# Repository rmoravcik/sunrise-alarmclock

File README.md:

Sunrise Alarm Clock

A [Philips Wake-Up Light](http://www.usa.philips.com/c-p/HF3505_60/wake-up-light) inspired alarm clock based on:

* Atmel ATmega328p
* RTC DS1307
* Bluetooth module HC-05 for remote configuration (Android application)
* WTV020 MP3 module for audio output

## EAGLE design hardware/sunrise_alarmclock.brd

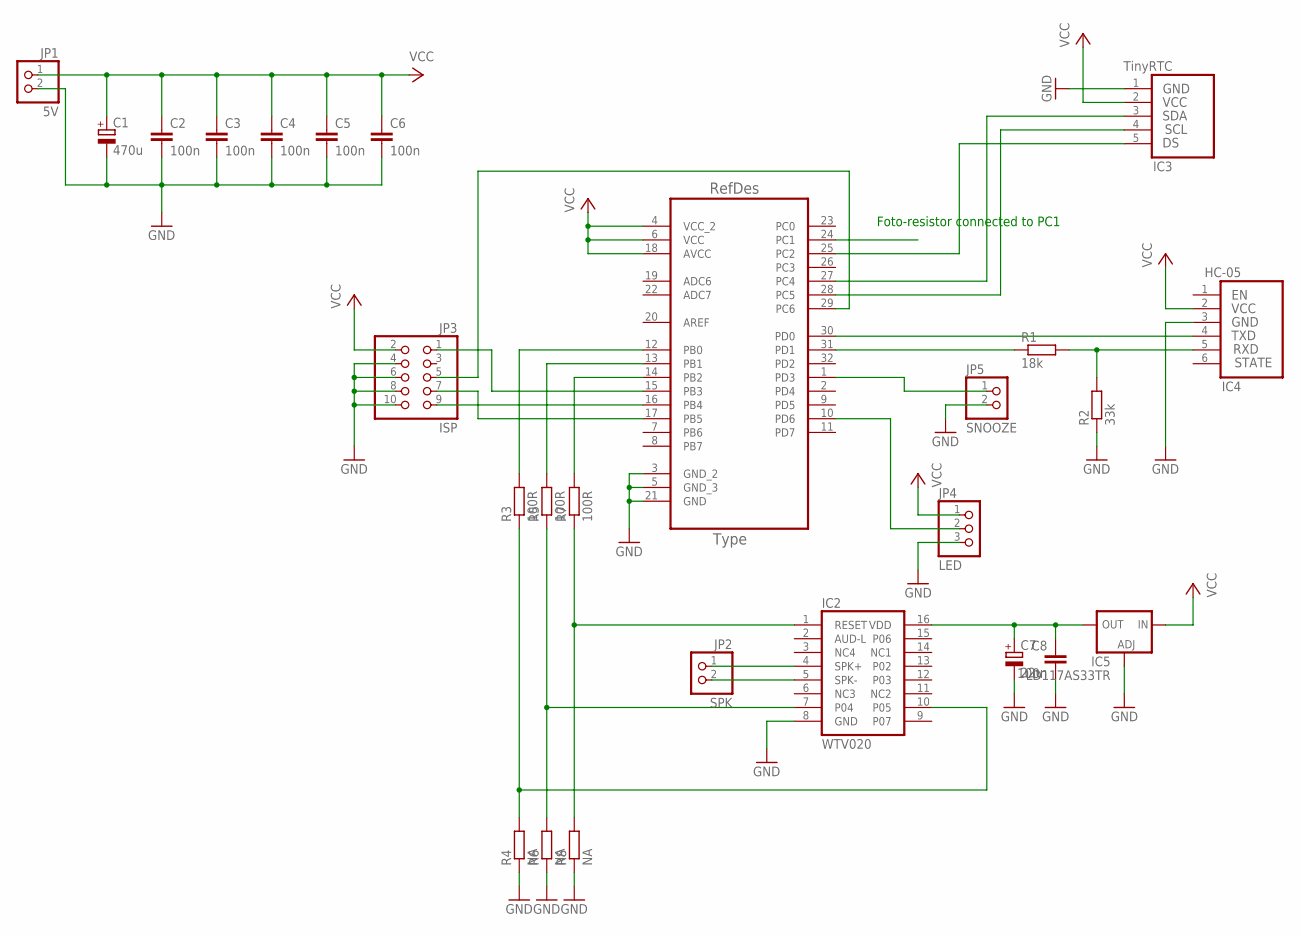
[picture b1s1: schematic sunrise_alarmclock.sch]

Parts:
C1: 470u; D/7343-31W
C2, C3, C4, C5, C6, C8: 100n; C1206K
C7: 22u; C/6032-28R
IC1: ATMEGA328P; QFP80P900X900X120-32N
IC2: WTV020; DIL16-6
IC3: TinyRTC; HC-05
IC4: HC-05
IC5: LD117AS33TR; SOT223
JP1: 5V; 1X02
JP2: SPK; 1X02
JP3: ISP; 2X05
JP4: LED; 1X03
JP5: SNOOZE; 1X02
R1: 18k; M1206
R2: 33k; M1206
R3, R5, R7: 100R; M1206
R4, R6, R8: NA; M1206

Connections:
GND: C1.-, C2.2, C3.2, C4.2, C5.2, C6.2, C7.-, C8.2, IC1.3 (GND_2), IC1.5 (GND_3), IC1.21 (GND), IC2.8 (GND), IC3.1 (GND), IC4.3 (GND), IC5.1 (ADJ), JP1.2, JP3.4, JP3.6, JP3.8, JP3.10, JP4.3, JP5.2, R2.1, R4.1, R6.1, R8.1
unnamed: IC1.15 (PB3), JP3.1
unnamed: IC1.29 (PC6), JP3.5
unnamed: IC1.17 (PB5), JP3.7
unnamed: IC1.16 (PB4), JP3.9
unnamed: IC1.31 (PD1), R1.1
unnamed: IC4.5 (RXD), R1.2, R2.2
unnamed: IC2.4 (SPK+), JP2.1
unnamed: IC1.28 (PC5), IC3.4 (SCL)
unnamed: IC1.27 (PC4), IC3.3 (SDA)
unnamed: IC2.5 (SPK-), JP2.2
unnamed: IC2.1 (RESET), R7.1, R8.2
unnamed: IC1.30 (PD0), IC4.4 (TXD)
unnamed: IC2.7 (P04), R5.1, R6.2
unnamed: IC2.10 (P05), R3.1, R4.2
unnamed: IC1.12 (PB0), R3.2
unnamed: IC1.25 (PC2), IC3.5 (DS)
unnamed: C7.+, C8.1, IC2.16 (VDD), IC5.4 (OUT)
unnamed: IC1.13 (PB1), R5.2
unnamed: IC1.14 (PB2), R7.2
unnamed: IC1.10 (PD6), JP4.2
unnamed: IC1.1 (PD3), JP5.1
VCC: C1.+, C2.1, C3.1, C4.1, C5.1, C6.1, IC1.4 (VCC_2), IC1.6 (VCC), IC1.18 (AVCC), IC3.2 (VCC), IC4.2 (VCC), IC5.3 (IN), JP1.1, JP3.2, JP4.1

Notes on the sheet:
Foto-resistor connected to PC1

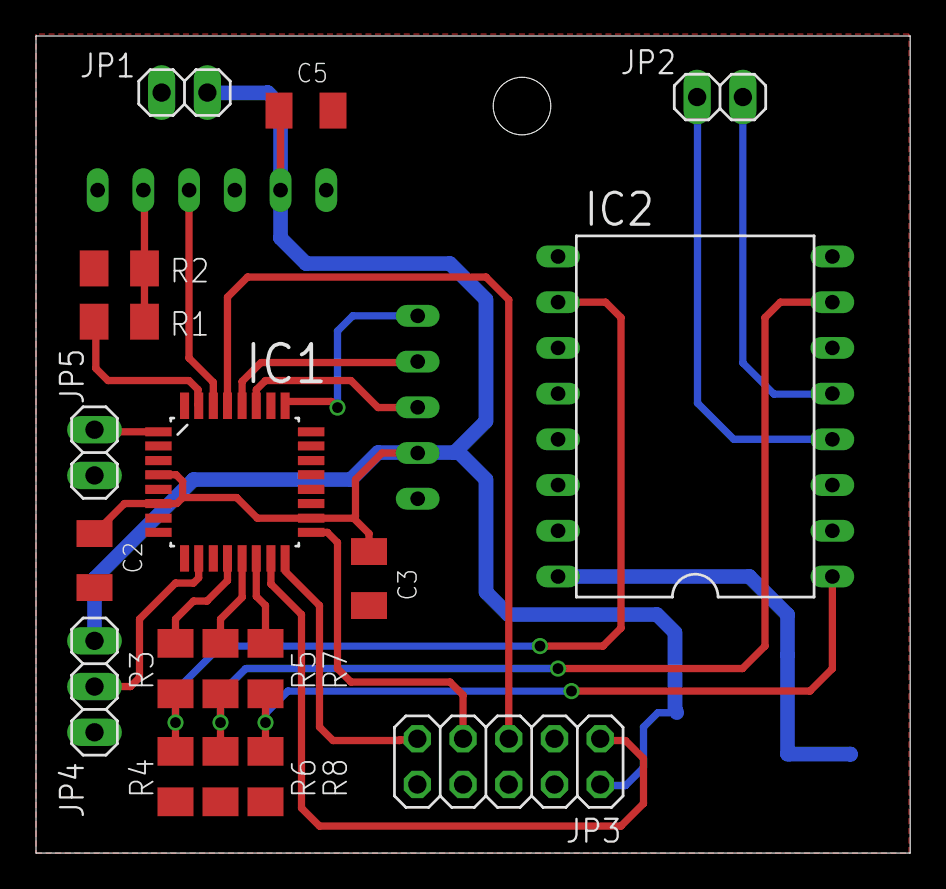
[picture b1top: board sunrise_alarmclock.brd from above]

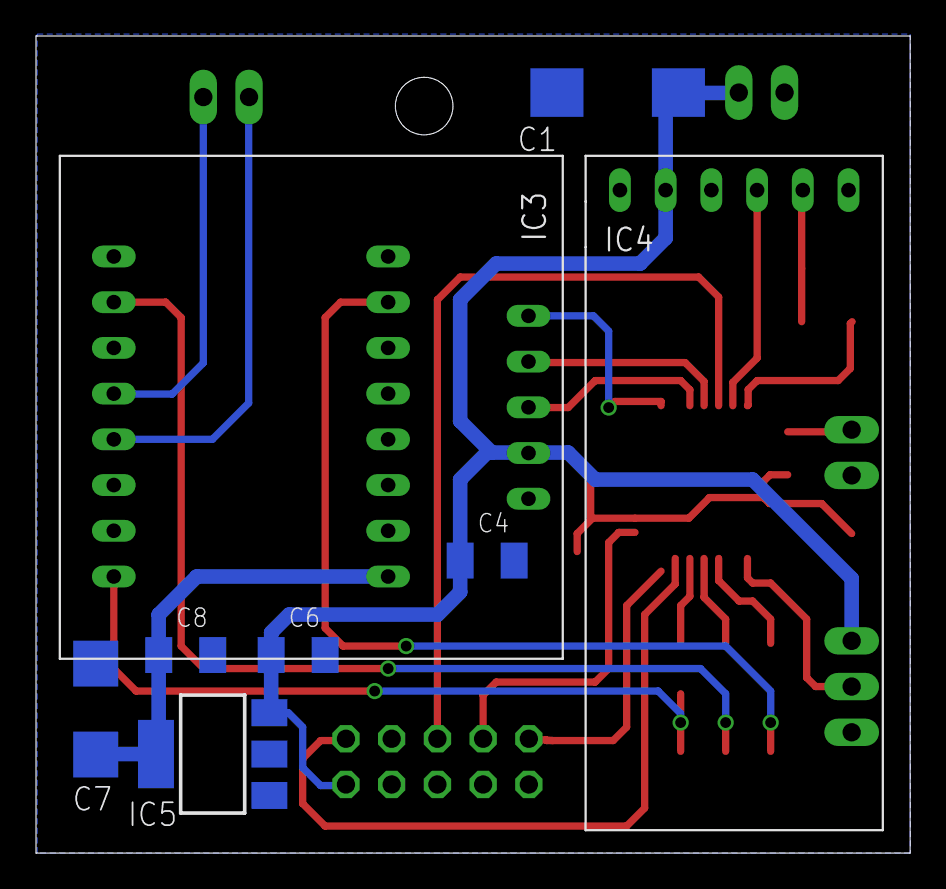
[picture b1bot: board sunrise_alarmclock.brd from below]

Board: 2 copper layers, 48.6 x 45.4 mm, 26 parts (8 on the bottom side), 23 nets.

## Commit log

2016-10-26 Added prototype hardware design.
2016-10-26 Added first android app based on google bluetooth chat
2016-10-26 client: Fix connection to HC-05
2016-10-26 firmware: Added demo based on DS RTC Library by Akafugu Corporation
2016-10-27 client: added Command class
2016-10-27 firmware: Added ssd1306xled library by Neven Boyanov
2016-10-27 firmware: added git submodule
2016-10-27 firmware: first cleanup of code.
2016-10-28 firmware: added first commands
2016-10-29 firmware: added support for twi lib from ds_rtc_lib in ssd1306xled.
2016-10-29 client: fixed communication with hw
2016-10-30 client: added command ping
2016-10-30 client: removed debugging code. make switch disabled by default.
2016-10-30 firmware: move alarm checking to irq from rtc
2016-10-31 firmware: added rtc2 wrapper
2016-11-01 firmware: switch to internal 8MHz RC oscilator.
2016-11-01 firmware: update submodule
2016-11-01 firmware: updated .gitmodules
2016-11-01 firmware: added light_ws2812 library
2016-11-01 firmware: updated light_ws2812 submodule
2016-11-01 firmware: first not fully working sunrise simulation.
2016-11-02 firmware: improved sunrise effect
2016-11-02 firmware: added simple FSM.
2016-11-02 client: fixed connection to device. added a connecting dialog.
2016-11-02 firmware: updated .gitignore
2016-11-02 firmware: simple sunset function
2016-11-03 firmware: use cr instead of lf in the debug mode
2016-11-03 firmware: added missing header
2016-11-03 firmware: try to set prealarm/alarm on device startup.
2016-11-03 firmware: fixed setting/clearing alarm by command
2016-11-03 firmware: removed useless debug print. invoke ISR for PC2 every 1sec instead of 500ms
2016-11-03 firmware: fixed period calculation
2016-11-03 firmware: added function to calc next wday. fixed reset of alarms during startup.
2016-11-03 firmware: fixed macro TO_SEC(). improved sunset effect
2016-11-03 client: fixed reading of day of week
2016-11-04 firmware: update leds every 500ms instead of 1 sec.
2016-11-04 firmware: added debug command to control leds.
2016-11-05 hardware: added components values
2016-11-06 firmware: improved sunrise simulation.
2016-11-21 firmware: Working display.
2016-11-22 firmware: added 25x32 font.
2016-11-22 firmware: turn on display for a 10 seconds after button press or during the alarm
2016-11-22 firmware: rtc2 renamed to rtc_wrapper
2016-11-22 firmware: added audio playback (not tested yet)
2016-11-22 firmware: added copyright headers
2016-11-22 firmware: start playback with lowest possible volume.
2016-11-23 firmware: audio code optimization.
2016-11-23 firmware: fix blinking of display during of alarm.
2016-11-24 firmware: first working audio.
2016-11-27 firmware: play alarm twice. fixed alarm volume.
2016-11-27 firmware: do not turn on leds if alarm is going to be turn on without prealarm.
2017-02-20 firmware: Fixed clearing of alarm if alarm on the next day is off.
2017-02-21 firmware: Added a simple light sensor.
2017-02-21 firmware: Check update of display every 500ms to speed up response to button press.
2017-02-25 firmware: disable alarm if prealarm was stopped.
2017-02-28 firmware: short press of button will stop prealarm and alarm immediately.
2017-02-28 case: added top_cover of case.
2017-02-28 case: added bottom_cover.
2017-03-01 case: added led_holder.
2017-03-01 case: working version of main_body of case.
2017-03-09 firmware: Added fork of ESP_WebConfig by John Lassen.
2017-03-10 firmware: removed general page.
2017-03-10 firmware: added very simple root page. needs clean up.
2017-03-10 firmware: fixed navigation.
2017-03-12 firmware: fixed alarm starting at midnight. Manual snooze button replaced by touch sensor with TTP223b.
2017-03-18 case: added speaker holder. fixed led_holder. main_body optimization.
2017-03-18 case: main_body translation
2017-04-06 firmware: refactoring code
2017-04-06 firmware: esp_webconfig refactoring 2.
2017-04-07 firmware: refactoring of network configuration page.
2017-04-10 firmware: implemented alarm setting page.
2017-04-19 firmware: esp_webconfig fixes
2017-04-19 firmware: fixed update of clock after alarm timeout
2017-04-19 fixmware: fixed captive portal. added reconnection to network if again available.
2017-04-19 firmware: removed ntp time from information page.
2017-04-20 firmware: added parsing of ntp response.
2017-04-24 firmware: added and fixed calculation of local time from ntp timestamp.
2017-04-25 firmware: added command ping and set time.
2017-04-25 firmware added command to set alarms.
2017-04-25 firmware: added retry of ntp request if response was not received.
2017-04-25 firmware: check configuration stored in mega and align it if it differs
2017-04-25 firmware: added copyright header.
2017-04-25 firmware: updated copyright headers.
2017-05-03 firmware: added alarm time range checks. removed whitespaces from code.
2017-05-03 hardware: fixed values of resistor towards the voice module. added note about connection of photo resistor to pin PC1
2017-05-29 firmware: speedup processing of serial commands.
2017-05-29 firmware: wait till firmware in atmega is ready processing serial commands.
2017-06-05 Fixed issue #1
2019-01-02 Print debug only when WIFI status changed.
2019-01-03 Added log.html page.
2019-01-03 Added LOG_EVENT_NTP_RESPONSE_TIMEOUT.
2019-01-03 Log not handled Wifi status changes.
2019-01-03 Log shortcut added to main configuration page.
2019-01-03 Removed ifdef from Configuration page.
2019-01-03 Fixed Wifi logging with SERIAL_DEBUG disabled.
2019-01-04 Added flushing of receive udp buffer
2019-01-04 Better flushing of UDP RxBuf
2019-01-04 Send mDNS response on every connect.
2019-01-04 Param -> Parameter
